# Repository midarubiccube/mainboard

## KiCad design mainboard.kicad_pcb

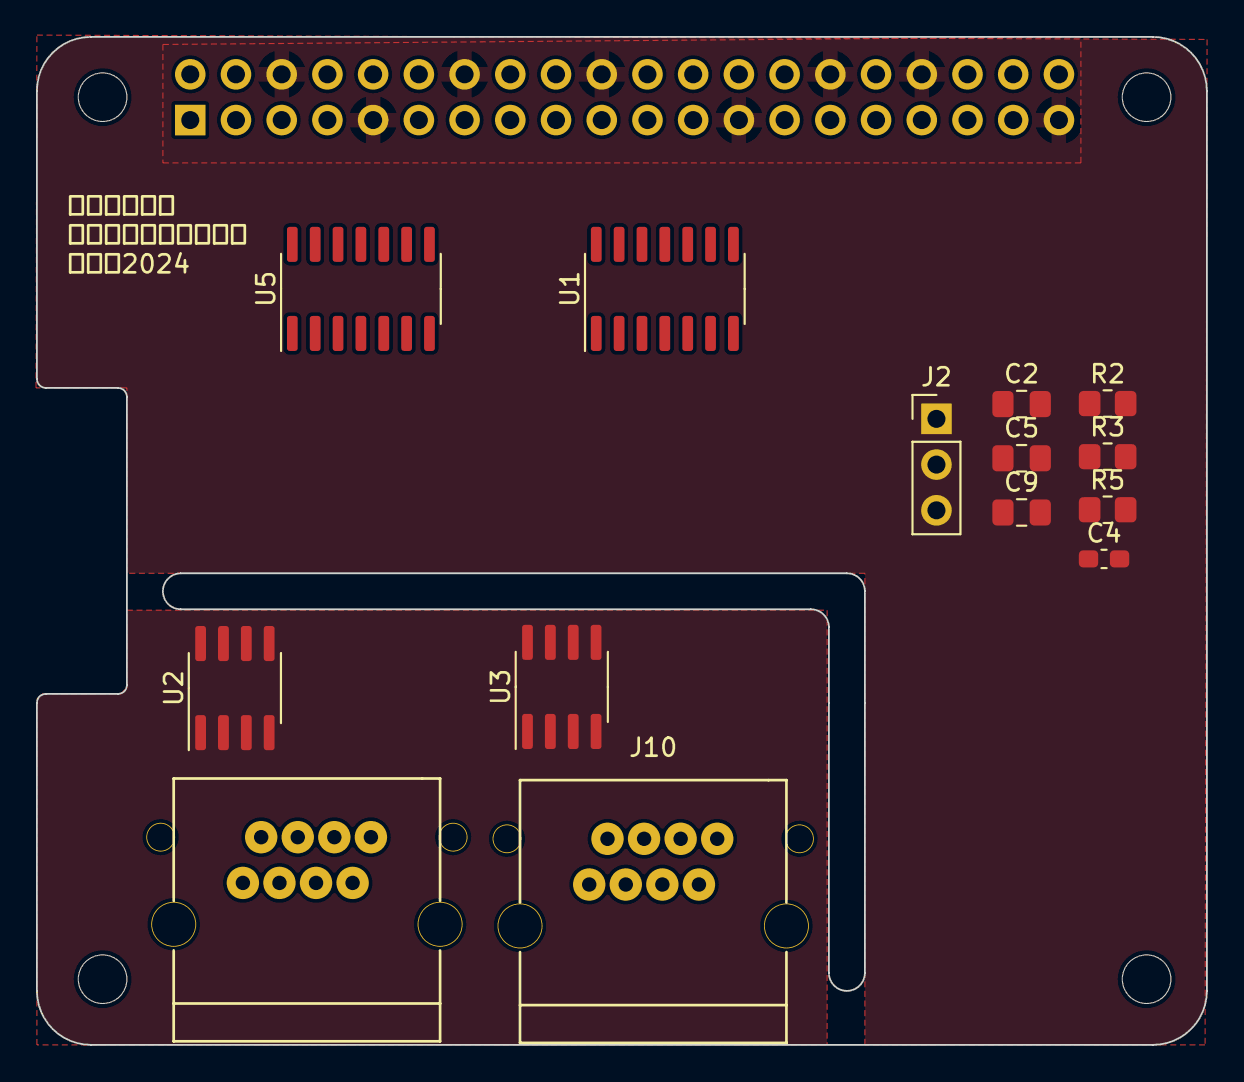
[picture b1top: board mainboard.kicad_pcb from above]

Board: 2 copper layers, 65.0 x 56.0 mm, 19 parts (1 on the bottom side), 12 nets, no tracks yet.

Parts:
C2: 10µF; C_0805_2012Metric_Pad1.18x1.45mm_HandSolder
C4: 0.1μF; C_0603_1608Metric_Pad1.08x0.95mm_HandSolder
C5: 10μF; C_0805_2012Metric_Pad1.18x1.45mm_HandSolder
C9: 22μF; C_0805_2012Metric_Pad1.18x1.45mm_HandSolder
J2: Conn_01x03_Socket; PinHeader_1x03_P2.54mm_Vertical
J9, J10: RJ45; 7810-8P8C
J12: GPIO; PinSocket_2x20_P2.54mm_Vertical
MH1, MH2, MH3, MH4: MountingHole_2.7mm_M2.5
R2: 330Ω; R_0805_2012Metric_Pad1.20x1.40mm_HandSolder
R3: 1kΩ; R_0805_2012Metric_Pad1.20x1.40mm_HandSolder
R5: 10Ω; R_0805_2012Metric_Pad1.20x1.40mm_HandSolder
U1, U5: MCP2517FD-xSL; SOIC-14_3.9x8.7mm_P1.27mm
U2, U3: MCP2562-E-SN; SOIC-8_3.9x4.9mm_P1.27mm

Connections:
+5V: C4.1, C5.1, J12.2, J12.4
+12V: C9.1, J9.4, J9.5, J10.4, J10.5
GND: C2.2, C4.2, C5.2, C9.2, J2.1, J9.7, J9.8, J10.7, J10.8, J12.6, J12.9, J12.14, J12.20, J12.25, J12.30, J12.34, J12.39, R5.2
INT: J12.22, U5.4 (~INT)
unnamed: J2.2, J9.2, J9.6, J10.2, J10.6
unnamed: J2.3, J9.1, J9.3, J10.1, J10.3
unnamed: R2.1, R3.2
unnamed: R2.2, R5.1
SPI0.CE0: J12.24, U5.13 (nCS)
SPI0.MISO: J12.21, U5.12 (SDO)
SPI0.MOSI: J12.19, U5.11 (SDI)
SPI0.SCLK: J12.23, U5.10 (SCK)

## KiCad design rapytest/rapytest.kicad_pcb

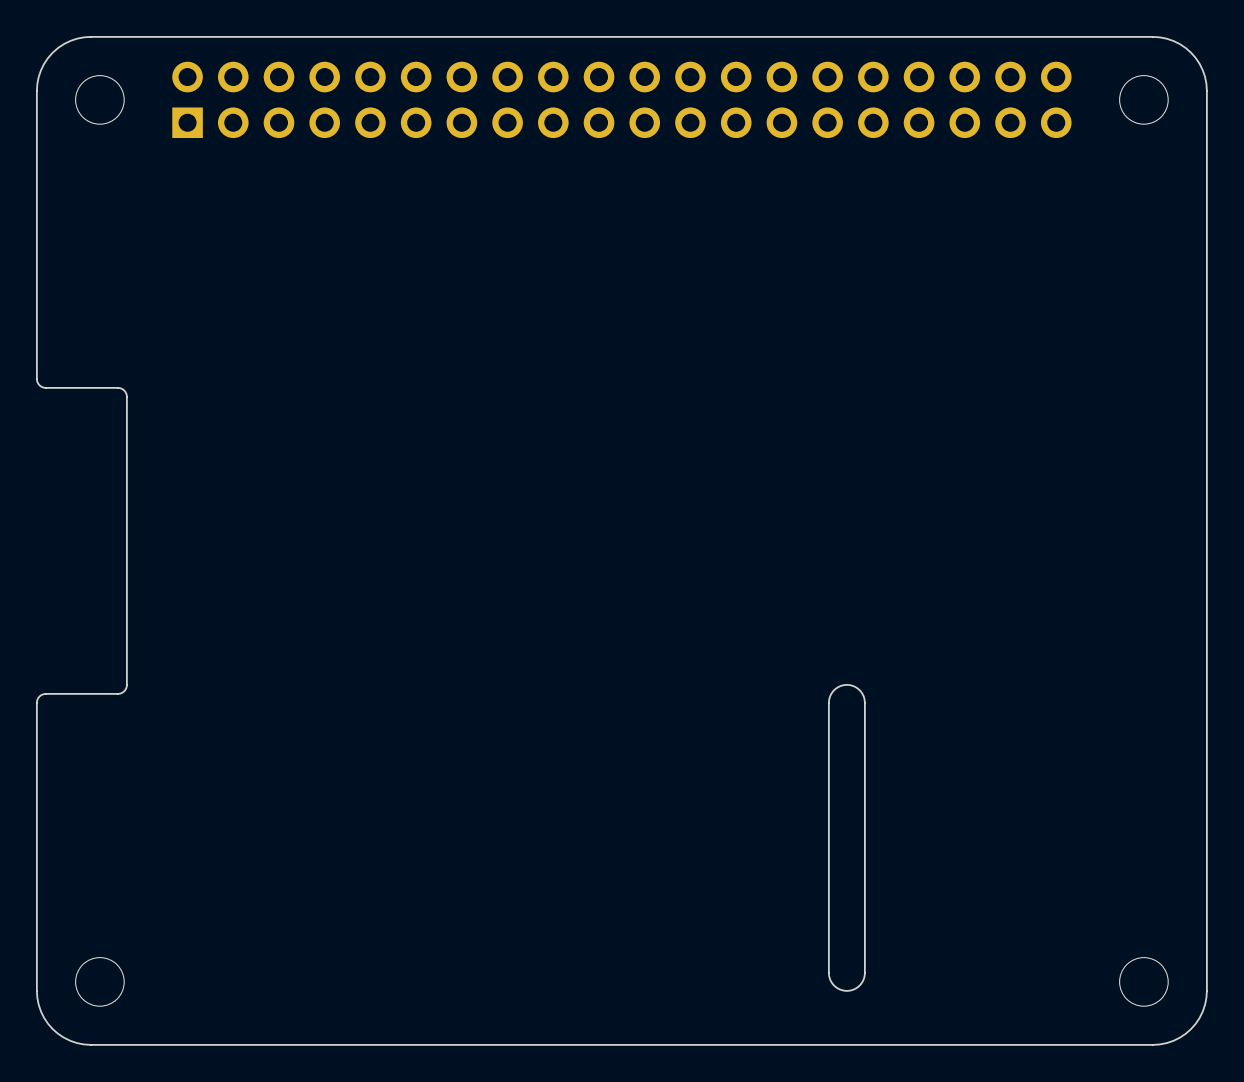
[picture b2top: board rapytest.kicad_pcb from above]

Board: 2 copper layers, 65.0 x 56.0 mm, 5 parts (1 on the bottom side), 3 nets, no tracks yet.

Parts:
J1: GPIO; PinSocket_2x20_P2.54mm_Vertical
MH1, MH2, MH3, MH4: MountingHole_2.7mm_M2.5

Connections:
+3V3: J1.1, J1.17
+5V: J1.2, J1.4
GND: J1.6, J1.9, J1.14, J1.20, J1.25, J1.30, J1.34, J1.39

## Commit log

2024-02-14 LEDを配線
2024-02-15 チップ抵抗に変更
2024-09-26 2chに変更
